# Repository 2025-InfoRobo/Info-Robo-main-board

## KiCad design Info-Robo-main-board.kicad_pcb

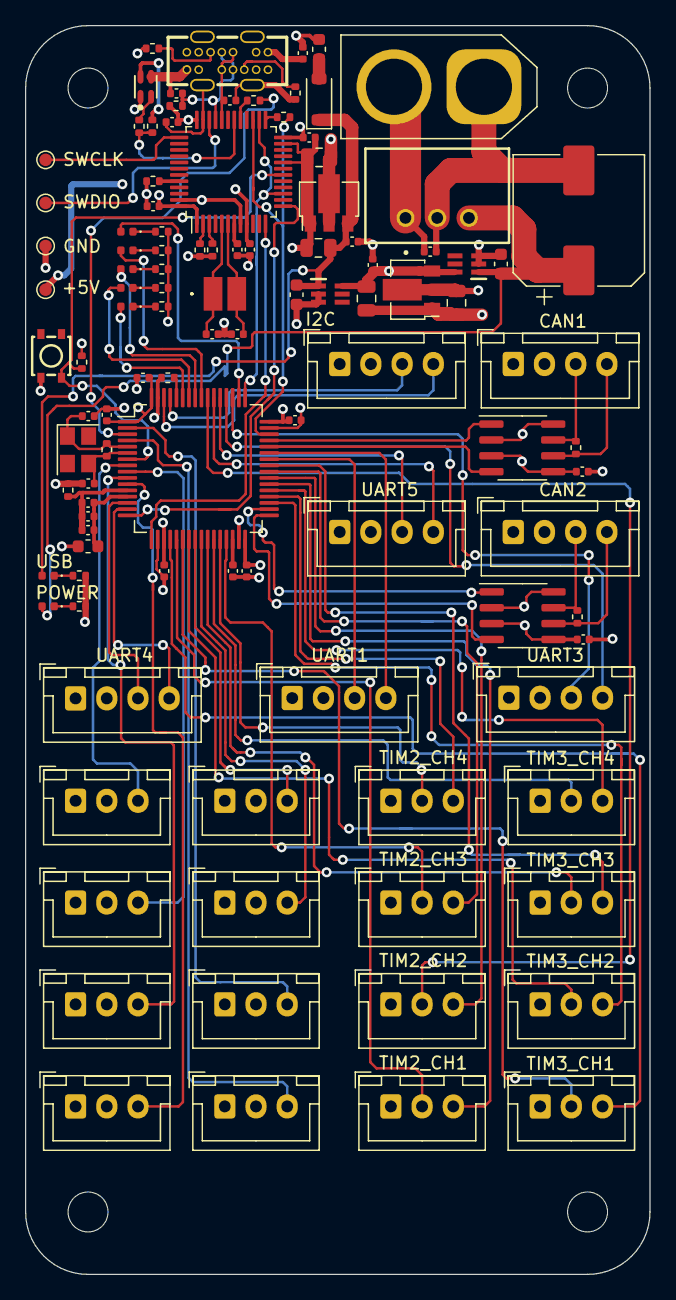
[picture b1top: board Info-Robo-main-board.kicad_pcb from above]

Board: 4 copper layers, 50.0 x 100.0 mm, 112 parts (0 on the bottom side), 92 nets.

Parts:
C101, C102: 1uF; C_0603_1608Metric
C103, C105, C213, C215: 10uF; C_0805_2012Metric
C104, C106, C201, C208, C209, C210, C211, C212, C214, C304, C305, C306, C307, C308, C310, C401, C501: 0.1uF; C_0402_1005Metric
C107: 220uF; CP_Elec_10x10
C202, C203: 47pF; C_0402_1005Metric
C206, C207: 10pF; C_0402_1005Metric
C301, C302: 20pF; C_0402_1005Metric
C303: 4.7uF; C_0402_1005Metric
C309: 0.01uF; C_0402_1005Metric
C311: 1uF; C_0402_1005Metric
D101, D102, D103, D104, D105: LED_Small; LED_0402_1005Metric
D106, D107: POWER; LED_0402_1005Metric
D201: D_Shockley; D_SOD-123
D202: LED_Dual_AAKK; LED-SMD_4P-L1.6-W1.6-BL-RD
FB201: FerriteBead_Small; L_0603_1608Metric
H101, H102, H103, H104: M3; MountingHole_3.2mm_M3
IC101, IC102: LM66100DCKT; SOT65P210X110-6N
IC103: M78AR05-0.5; M78AR05
J101: XT60; AMASS_XT60-M_1x02_P7.20mm_Vertical
J102, J103, J104, J105, J106, J107, J108: XH_4P; JST_XH_B4B-XH-A_1x04_P2.50mm_Vertical
J109, J110, J111, J112, J113, J114, J115, J116, J117, J118, J119, J120, J121, J122, J123, J124: XH_3P; JST_XH_B3B-XH-A_1x03_P2.50mm_Vertical
J201: TYPE-C-14PLC-H10.0; USB-C-TH_SHOUHAN_TYPE-C-14PLC-H10.0
J202, J203, J204, J205: Conn_01x01; TestPoint_Pad_D1.0mm
L301: L_Small; L_0603_1608Metric
R101, R102, R103, R104, R105, R106, R107, R208, R301, R302: 4.7k; R_0402_1005Metric
R201, R202: 5.1k; R_0402_1005Metric
R203: 100k; R_0402_1005Metric
R204, R205: 10k; R_0402_1005Metric
R206, R207: 100; R_0402_1005Metric
R209, R210: 4.7K; R_0402_1005Metric
R303: 1M; R_0402_1005Metric
R304: 0; R_0402_1005Metric
R401, R501: 120; R_0402_1005Metric
SW301: SW_Push_45deg; SW-SMD_4P-L3.0-W2.8-P1.65-TL_GT-TS171A-H014-L1
U101, U202: AMS1117-3.3; SOT-89-3
U201: STM32F103CBTx; LQFP-48_7x7mm_P0.5mm
U301: STM32F446RETx; LQFP-64_10x10mm_P0.5mm
U401, U501: MCP2562-E-P; SOIC-8_3.9x4.9mm_P1.27mm
Y201: NX3225GD-8MHZ-STD-CRA-3; NX3225GD8MHZSTDCRA3
Y301: SX3B16.000F1510F30; Crystal_SMD_3225-4Pin_3.2x2.5mm

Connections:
+3.3V: C105.1, C304.1, C305.1, C306.1, C307.1, C308.1, L301.1, R302.1, U101.2 (VO), U301.1 (VBAT), U301.19 (VDD), U301.32 (VDD), U301.48 (VDD), U301.64 (VDD)
+3.3VA: C309.1, C310.1, C311.1, L301.2, U301.13 (VDDA)
+5V: C103.1, C104.1, C401.1, C501.1, IC101.6 (VOUT), IC102.6 (VOUT), J102.2, J103.2, J104.2, J105.2, J106.2, J107.2, J108.2, J117.2, J118.2, J119.2, J120.2, J121.2, J122.2, J123.2, J124.2, U101.3 (VI), U401.3 (VDD), U401.5 (Vio), U501.3 (VDD), U501.5 (Vio)
/CAN1/CANH: J107.3, R401.1, U401.7 (CANH)
/CAN1/CANL: J107.4, R401.2, U401.6 (CANL)
/CAN1_RX: U301.44 (PA11), U401.4 (RXD)
/CAN1_TX: U301.45 (PA12), U401.1 (TXD)
/CAN2/CANH: J108.3, R501.1, U501.7 (CANH)
/CAN2/CANL: J108.4, R501.2, U501.6 (CANL)
/CAN2_RX: U301.33 (PB12), U501.4 (RXD)
/CAN2_TX: U301.34 (PB13), U501.1 (TXD)
/GPIO_in_PC0: J117.3, U301.8 (PC0)
/GPIO_in_PC1: J118.3, U301.9 (PC1)
/GPIO_in_PC2: J119.3, U301.10 (PC2)
/GPIO_in_PC3: J120.3, U301.11 (PC3)
/GPIO_in_PC4: J121.3, U301.24 (PC4)
/GPIO_in_PC5: J122.3, U301.25 (PC5)
/GPIO_in_PC13: J123.3, U301.2 (PC13)
/GPIO_in_PC15: J124.3, U301.4 (PC15)
/GPIO_out_PA4: J113.3, U301.20 (PA4)
/GPIO_out_PA8: J115.3, U301.41 (PA8)
/GPIO_out_PA15: D101.2 (A), U301.50 (PA15)
/GPIO_out_PB4: D102.2 (A), U301.56 (PB4)
/GPIO_out_PB5: D103.2 (A), U301.57 (PB5)
/GPIO_out_PB6: D104.2 (A), U301.58 (PB6)
/GPIO_out_PB7: D105.2 (A), U301.59 (PB7)
/GPIO_out_PB14: J114.3, U301.35 (PB14)
/GPIO_out_PB15: J112.3, U301.36 (PB15)
/GPIO_out_PC6: J116.3, U301.37 (PC6)
/GPIO_out_PC7: J109.3, U301.38 (PC7)
/GPIO_out_PC8: J110.3, U301.39 (PC8)
/GPIO_out_PC9: J111.3, U301.40 (PC9)
/I2C_SCL: J106.3, U301.61 (PB8)
/I2C_SDA: J106.4, U301.62 (PB9)
/MCO: R207.2, U301.3 (PC14)
/NRST: R302.2, SW301.2, U201.18 (PB0), U301.7 (NRST)
/ST-LinkV2_1/PD0: C206.1, U201.5 (PD0), Y201.1
/ST-LinkV2_1/PD1: C207.1, U201.6 (PD1), Y201.2
/ST-LinkV2_1/ST-LIN3V3: C209.1, C210.1, C211.1, C212.1, C215.1, D202.1 (A1), J205.1, R208.1, U201.1 (VBAT), U201.9 (VDDA), U201.24 (VDD), U201.36 (VDD), U201.48 (VDD), U202.2 (VO)
/ST-LinkV2_1/STLink_NRST: C208.1, U201.7 (NRST)
/ST-LinkV2_1/STLink_SWCLK: J202.1, U201.37 (PA14)
/ST-LinkV2_1/STLink_SWDIO: J203.1, U201.34 (PA13)
/ST-LinkV2_1/STLink_TX: R209.1, R210.2, U201.30 (PA9)
/ST-LinkV2_1/T_SWDIO_IN: R206.2, U201.25 (PB12)
/ST-LinkV2_1/USB_DM: C203.1, J201.A7 (DN1), J201.B7 (DN2), U201.32 (PA11)
/ST-LinkV2_1/USB_DP: C202.1, J201.A6 (DP1), J201.B6 (DP2), R208.2, U201.33 (PA12)
/STM32F446RET6/BOOT0: R301.1, U301.60 (BOOT0)
/STM32F446RET6/PH0: C301.1, R303.2, U301.5 (PH0), Y301.1
/STM32F446RET6/PH1: C302.1, R303.1, U301.6 (PH1), Y301.3
/TCK: U201.15 (PA5), U201.26 (PB13), U301.49 (PA14)
/TIM2_CH1: J109.2, U301.21 (PA5)
/TIM2_CH2: J110.2, U301.55 (PB3)
/TIM2_CH3: J111.2, U301.29 (PB10)
/TIM2_CH4: J112.2, U301.28 (PB2)
/TIM3_CH1: J113.2, U301.22 (PA6)
/TIM3_CH2: J114.2, U301.23 (PA7)
/TIM3_CH3: J115.2, U301.26 (PB0)
/TIM3_CH4: J116.2, U301.27 (PB1)
/TMS: R206.1, U201.27 (PB14), U301.46 (PA13)
/UART3_RX: J104.4, U301.52 (PC11)
/UART3_TX: J104.3, U301.51 (PC10)
/UART4_RX: J102.4, U301.15 (PA1)
/UART4_TX: J102.3, U301.14 (PA0)
/UART5_RX: J105.4, U301.54 (PD2)
/UART5_TX: J105.3, U301.53 (PC12)
/USART1_RX: J103.4, U301.43 (PA10)
/USART1_TX: J103.3, U301.42 (PA9)
/USART_RX: U201.12 (PA2), U301.17 (PA3)
/USART_TX: U201.13 (PA3), U301.16 (PA2)
/VBUS_USB: C101.1, C213.1, C214.1, D106.2 (A), D201.1 (K), IC101.1 (VIN), U202.3 (VI)
/VIN: C102.1, C107.1, D107.2 (A), IC102.1 (VIN), IC103.3 (+VOUT)
GND: C101.2, C102.2, C103.2, C104.2, C105.2, C106.2, C107.2, C201.2, C202.2, C203.2, C206.2, C207.2, C208.2, C209.2, C210.2, C211.2, C212.2, C213.2, C214.2, C215.2, C301.2, C302.2, C303.2, C304.2, C305.2, C306.2, C307.2, C308.2, C401.2, C501.2, D202.4 (K2), IC101.2 (GND), IC101.3 (~CE), IC102.2 (GND), IC102.3 (~CE), IC103.2 (GND), J101.1, J102.1, J103.1, J104.1, J105.1, J106.1, J107.1, J108.1, J109.1, J110.1, J111.1, J112.1, J113.1, J114.1, J115.1, J116.1, J117.1, J118.1, J119.1, J120.1, J121.1, J122.1, J123.1, J124.1, J201.0 (SHELL), J201.A1 (GND), J201.A12 (GND), J201.B1 (GND), J201.B12 (GND), J204.1, R101.2, R102.2, R103.2, R104.2, R105.2, R106.2, R107.2, R201.1, R202.1, R203.1, R204.1, R205.1, R301.2, R304.1, SW301.1, U101.1 (GND), U201.8 (VSSA), U201.20 (PB2), U201.23 (VSS), U201.35 (VSS), U201.47 (VSS), U202.1 (GND), U301.18 (VSS), U301.31 (VSS), U301.47 (VSS), U301.63 (VSS), U401.2 (VSS), U401.8 (STBY), U501.2 (VSS), U501.8 (STBY)
GNDA: C309.2, C310.2, C311.2, R304.2, U301.12 (VSSA)
unnamed: C201.1, FB201.1, J201.A4 (VBUS), J201.A9 (VBUS), J201.B4 (VBUS), J201.B9 (VBUS)
unnamed: D101.1 (K), R101.1
unnamed: D102.1 (K), R102.1
unnamed: D103.1 (K), R103.1
unnamed: D104.1 (K), R104.1
unnamed: D105.1 (K), R105.1
unnamed: D106.1 (K), R106.1
unnamed: D107.1 (K), R107.1
unnamed: D201.2 (A), FB201.2
unnamed: D202.2 (A2), R210.1
unnamed: D202.3 (K1), R209.2
unnamed: C106.1, IC103.1 (+VIN), J101.2
unnamed: J201.A5 (CC1), R202.2
unnamed: J201.B5 (CC2), R201.2
unnamed: R203.2, U201.44 (BOOT0)
unnamed: R207.1, U201.29 (PA8)
unnamed: R204.2, U201.2 (PC13)
unnamed: R205.2, U201.3 (PC14)
unnamed: C303.1, U301.30 (VCAP_1)

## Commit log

2025-02-15 complete design
2025-03-15 Fix ST-link reset
2025-04-09 シルク逆でしたごめんなさい
2025-04-13 add bin file for ST-Link
